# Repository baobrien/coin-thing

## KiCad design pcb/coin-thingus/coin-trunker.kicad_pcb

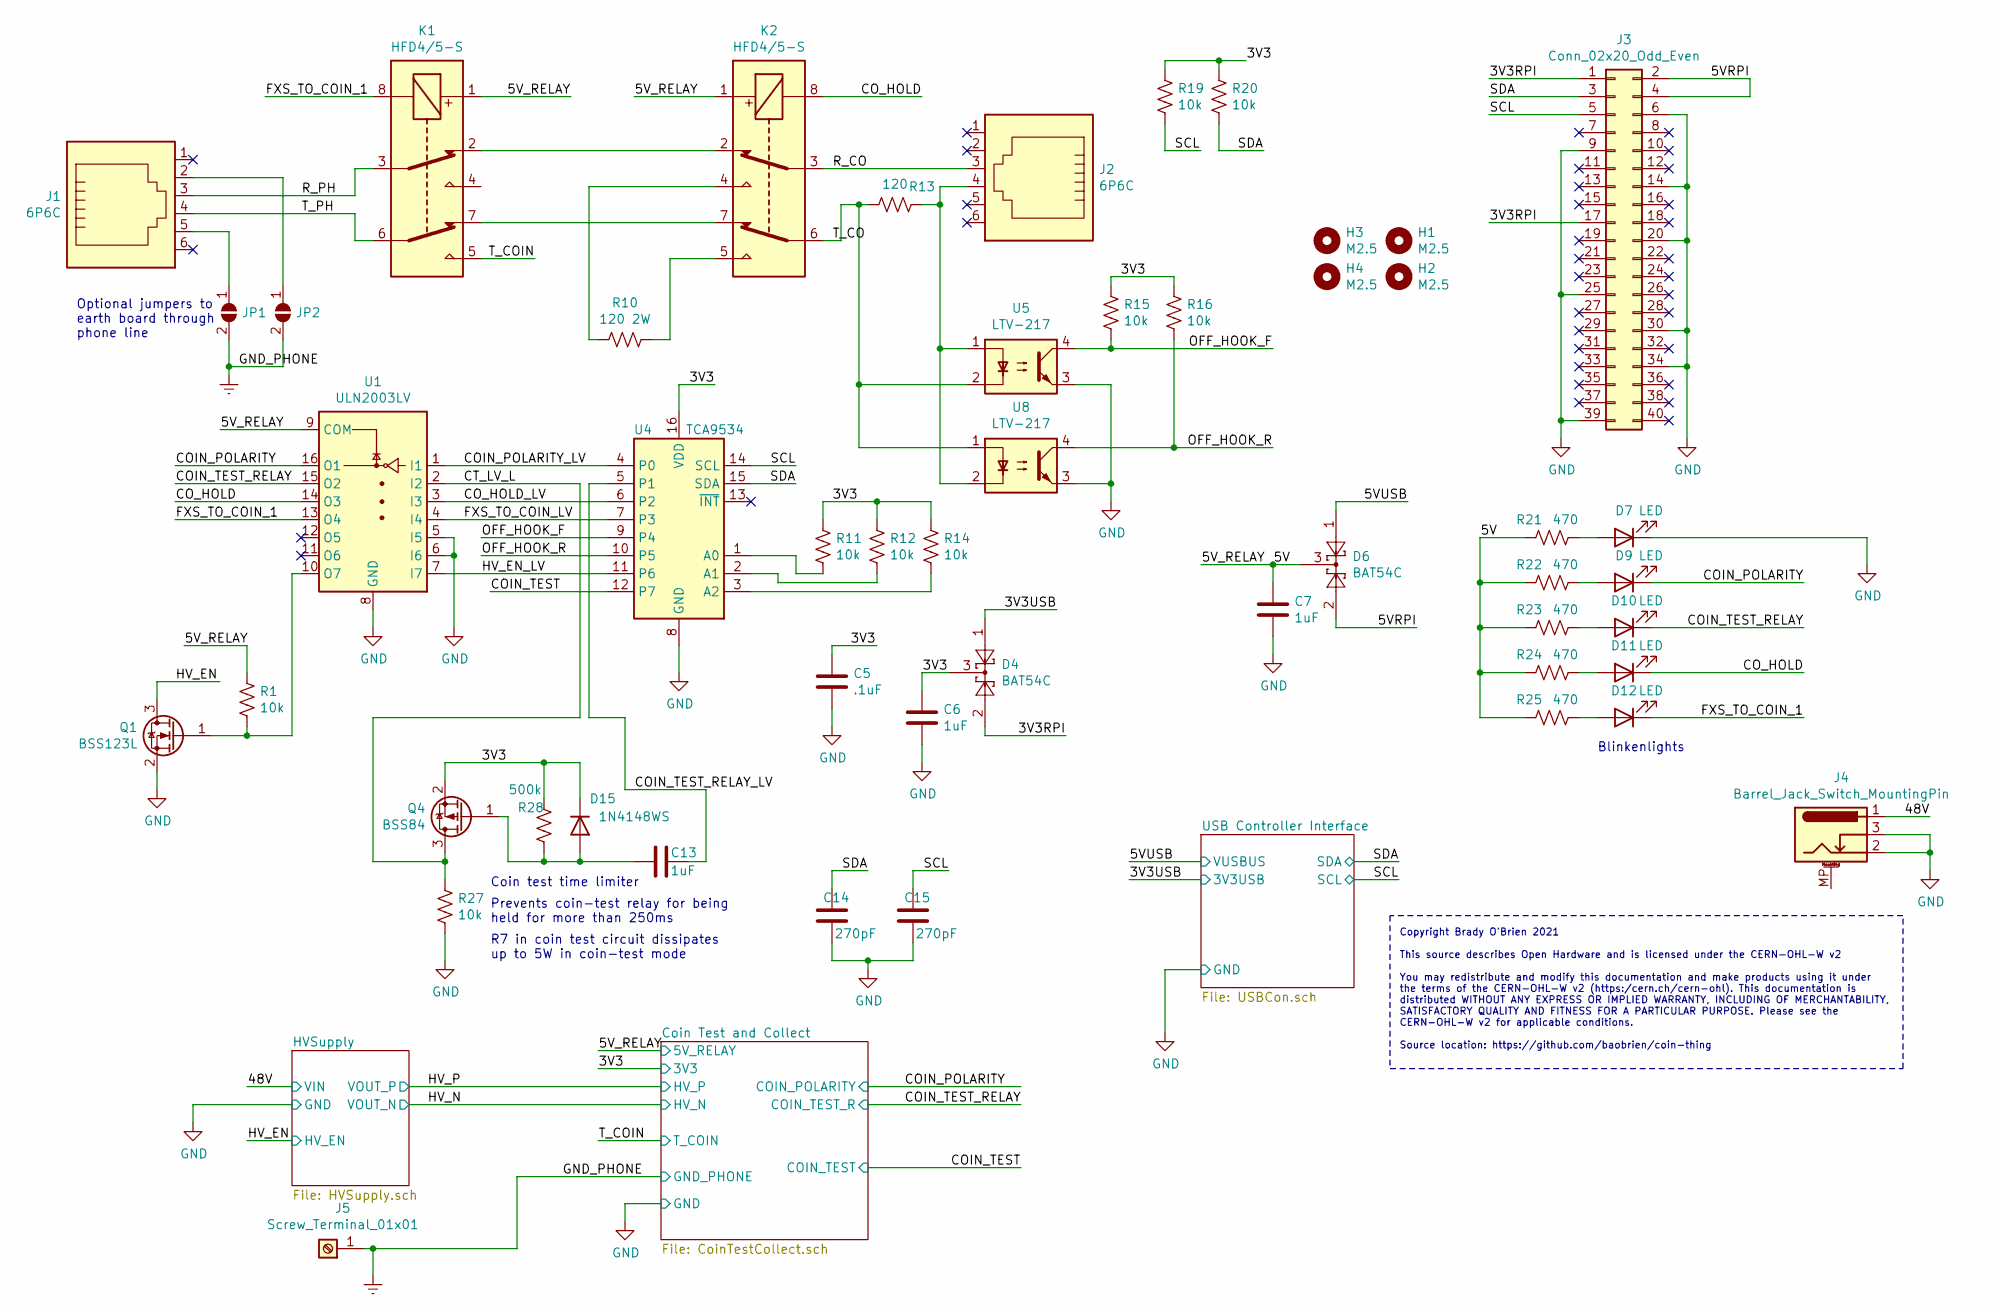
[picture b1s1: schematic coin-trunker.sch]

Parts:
C5: .1uF; C_0603_1608Metric
C6, C7, C13: 1uF; C_0603_1608Metric
C14, C15: 270pF; C_0603_1608Metric
D4, D6: BAT54C; SOT-23
D7, D9, D10, D11, D12: LED; LED_0603_1608Metric
D15: 1N4148WS; D_SOD-323_HandSoldering
H1, H2, H3, H4: M2.5; MountingHole_2.7mm_M2.5_Pad
J1, J2: 6P6C; RJ12_Molex_95501-6669
J3: Conn_02x20_Odd_Even; PinHeader_2x20_P2.54mm_Vertical
J4: Barrel_Jack_Switch_MountingPin; BarrelJack_CUI_PJ-102AH_Horizontal; Part PJ-102AH
J5: Screw_Terminal_01x01; screw_block_m3_5x7
JP1, JP2: SolderJumper_2_Open; SolderJumper-2_P1.3mm_Open_TrianglePad1.0x1.5mm
K1, K2: HFD4/5-S; Relay_DPDT_Omron_G6K-2F-Y
Q1: BSS123L; SOT-23
Q4: BSS84; SOT-23
R1, R11, R12, R14, R15, R16, R19, R20, R27: 10k; R_0402_1005Metric
R10: 120 2W; R_1206_3216Metric
R13: 120; R_0402_1005Metric
R21, R22, R23, R24, R25: 470; R_0402_1005Metric
R28: 500k; R_0402_1005Metric
U1: ULN2003LV; SOIC-16_3.9x9.9mm_P1.27mm
U4: TCA9534; TSSOP-16_4.4x5mm_P0.65mm
U5, U8: LTV-217; SOP-4_4.4x2.6mm_P1.27mm

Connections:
/3V3: C5.1, C6.1, D4.3, D15.1 (K), Q4.2 (S), R11.2, R12.2, R14.2, R15.2, R16.2, R19.2, R20.2, R28.1, U4.16 (VDD); also elsewhere on the board
/3V3RPI: D4.2, J3.1, J3.17
/3V3USB: D4.1; also elsewhere on the board
/5V: C7.1, D6.3, K1.1, K2.1, R1.1, R21.2, R22.2, R23.2, R24.2, R25.2, U1.9 (COM); also elsewhere on the board
/5VRPI: D6.2, J3.2, J3.4
/5VUSB: D6.1; also elsewhere on the board
/48V: J4.1; also elsewhere on the board
/COIN_POLARITY: D9.1 (K), U1.16 (O1); also elsewhere on the board
/COIN_POLARITY_LV: U1.1 (I1), U4.4 (P0)
/COIN_TEST: U4.12 (P7); also elsewhere on the board
/COIN_TEST_RELAY: D10.1 (K), U1.15 (O2); also elsewhere on the board
/COIN_TEST_RELAY_LV: C13.1, U4.5 (P1)
/CO_HOLD: D11.1 (K), K2.8, U1.14 (O3)
/CO_HOLD_LV: U1.3 (I3), U4.6 (P2)
/CT_LV_L: Q4.3 (D), R27.1, U1.2 (I2)
/FXS_TO_COIN_1: D12.1 (K), K1.8, U1.13 (O4)
/FXS_TO_COIN_LV: U1.4 (I4), U4.7 (P3)
/HV_EN: Q1.3 (D); also elsewhere on the board
/HV_EN_LV: U1.7 (I7), U4.11 (P6)
/OFF_HOOK_F: R15.1, U4.9 (P4), U5.4
/OFF_HOOK_R: R16.1, U4.10 (P5), U8.4
/R_CO: J2.3, K2.3
/R_PH: J1.3, K1.3
/SCL: C15.2, J3.5, R19.1, U4.14 (SCL); also elsewhere on the board
/SDA: C14.2, J3.3, R20.1, U4.15 (SDA); also elsewhere on the board
/T_CO: K2.6, R13.1, U5.2, U8.1
/T_COIN: K1.5; also elsewhere on the board
/T_PH: J1.4, K1.6
Earth: J5.1, JP1.2 (B), JP2.2 (B); also elsewhere on the board
GND: C5.2, C6.2, C7.2, C14.1, C15.1, D7.1 (K), J3.6, J3.9, J3.14, J3.20, J3.25, J3.30, J3.34, J3.39, J4.2, J4.3, Q1.2 (S), R27.2, U1.5 (I5), U1.6 (I6), U1.8 (GND), U4.8 (GND), U5.3, U8.3; also elsewhere on the board
unnamed: C13.2, D15.2 (A), Q4.1 (G), R28.2
unnamed: D7.2 (A), R21.1
unnamed: D9.2 (A), R22.1
unnamed: D10.2 (A), R23.1
unnamed: D11.2 (A), R24.1
unnamed: D12.2 (A), R25.1
unnamed: J1.2, JP2.1 (A)
unnamed: J1.5, JP1.1 (A)
unnamed: J2.4, R13.2, U5.1, U8.2
unnamed: K1.2, K2.2
unnamed: K1.7, K2.7
unnamed: K2.4, R10.2
unnamed: K2.5, R10.1
unnamed: Q1.1 (G), R1.2, U1.10 (O7)
unnamed: R11.1, U4.1 (A0)
unnamed: R12.1, U4.2 (A1)
unnamed: R14.1, U4.3 (A2)

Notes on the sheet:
Copyright Brady O’Brien 2021 This source describes Open Hardware and is licensed under the CERN-OHL-W v2 You may redistribute and modify this documentation and make products using it under the terms of the CERN-OHL-W v2 (https:/cern.ch/cern-ohl). This documentation is distributed WITHOUT ANY EXPRES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
Blinkenlights
Optional jumpers to earth board through phone line
Coin test time limiter
Prevents coin-test relay for being held for more than 250ms
R7 in coin test circuit dissipates up to 5W in coin-test mode

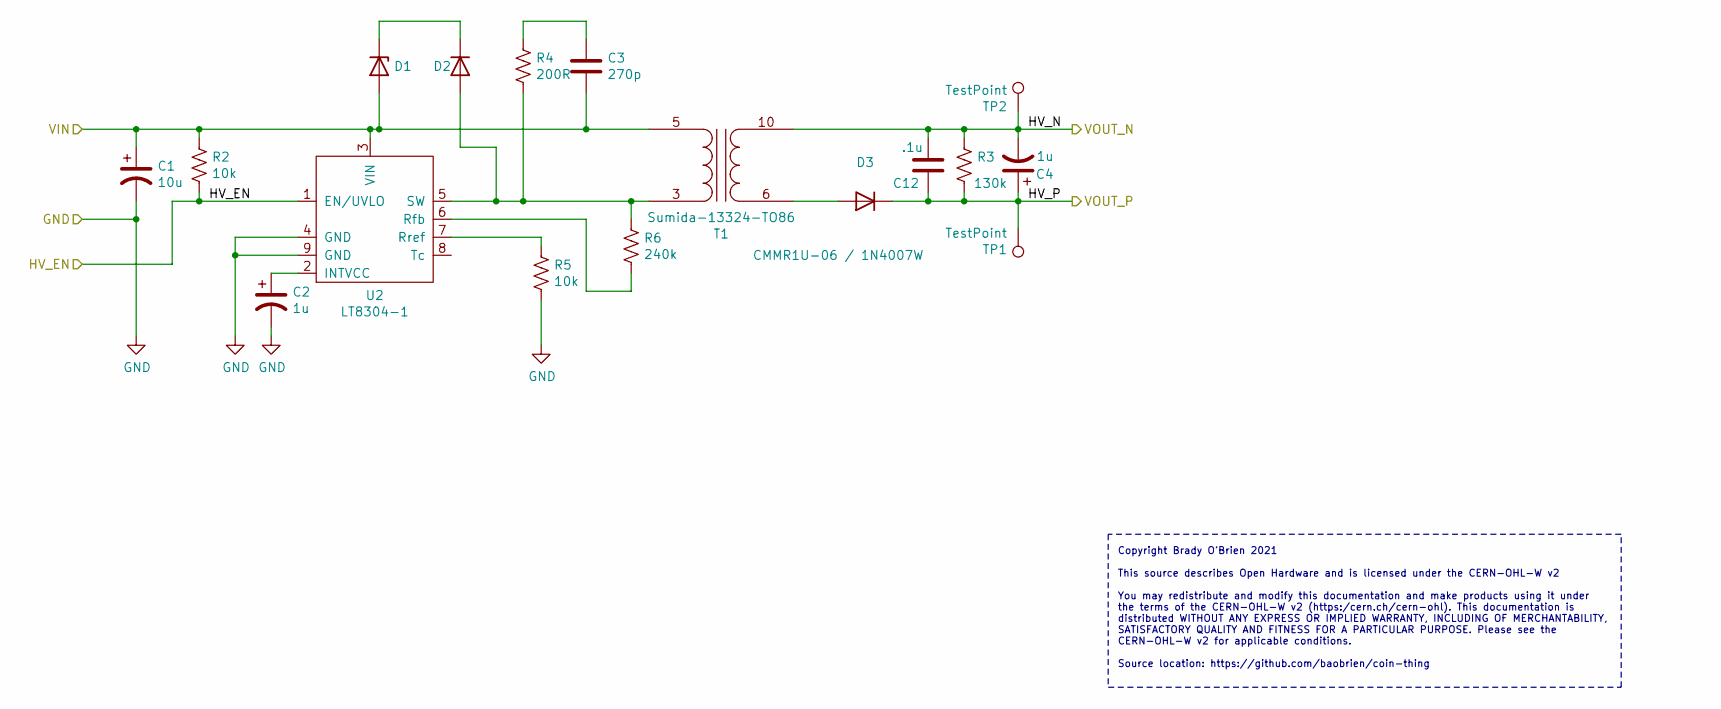
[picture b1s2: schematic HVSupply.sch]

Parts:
C1: 10u; C_1210_3225Metric
C2: 1u; C_0603_1608Metric
C3: 270p; C_0603_1608Metric
C4: 1u; CP_Radial_D6.3mm_P2.50mm
C12: .1u; C_1210_3225Metric
D1: D_Zener; D_SMA
D2: DFLS1150-7; D_PowerDI-123
D3: CMMR1U-06 / 1N4007W; D_SOD-123F; Part CMMR1U-06
R2, R5: 10k; R_0402_1005Metric
R3: 130k; R_0402_1005Metric
R4: 200R; R_0402_1005Metric
R6: 240k; R_0603_1608Metric
T1: Sumida-13324-TO86; SUMIDA-S-074-1511
TP1, TP2: TestPoint; Pin_D1.0mm_L10.0mm
U2: LT8304-1; TI_SO-PowerPAD-8

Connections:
/48V: C1.1, C3.2, D1.2 (A), R2.2, T1.5 (AB), U2.3 (VIN); also elsewhere on the board
/HV_EN: R2.1, U2.1 (EN/UVLO); also elsewhere on the board
/HV_N: C4.2, C12.1, R3.1, T1.10 (SA), TP2.1; also elsewhere on the board
/HV_P: C4.1, C12.2, D3.1 (K), R3.2, TP1.1; also elsewhere on the board
GND: C1.2, C2.2, R5.1, U2.4 (GND), U2.9 (GND); also elsewhere on the board
unnamed: C2.1, U2.2 (INTVCC)
unnamed: C3.1, R4.2
unnamed: D1.1 (K), D2.1 (K)
unnamed: D2.2 (A), R4.1, R6.1, T1.3 (AA), U2.5 (SW)
unnamed: D3.2 (A), T1.6 (SB)
unnamed: R5.2, U2.7 (Rref)
unnamed: R6.2, U2.6 (Rfb)

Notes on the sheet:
Copyright Brady O’Brien 2021 This source describes Open Hardware and is licensed under the CERN-OHL-W v2 You may redistribute and modify this documentation and make products using it under the terms of the CERN-OHL-W v2 (https:/cern.ch/cern-ohl). This documentation is distributed WITHOUT ANY EXPRES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

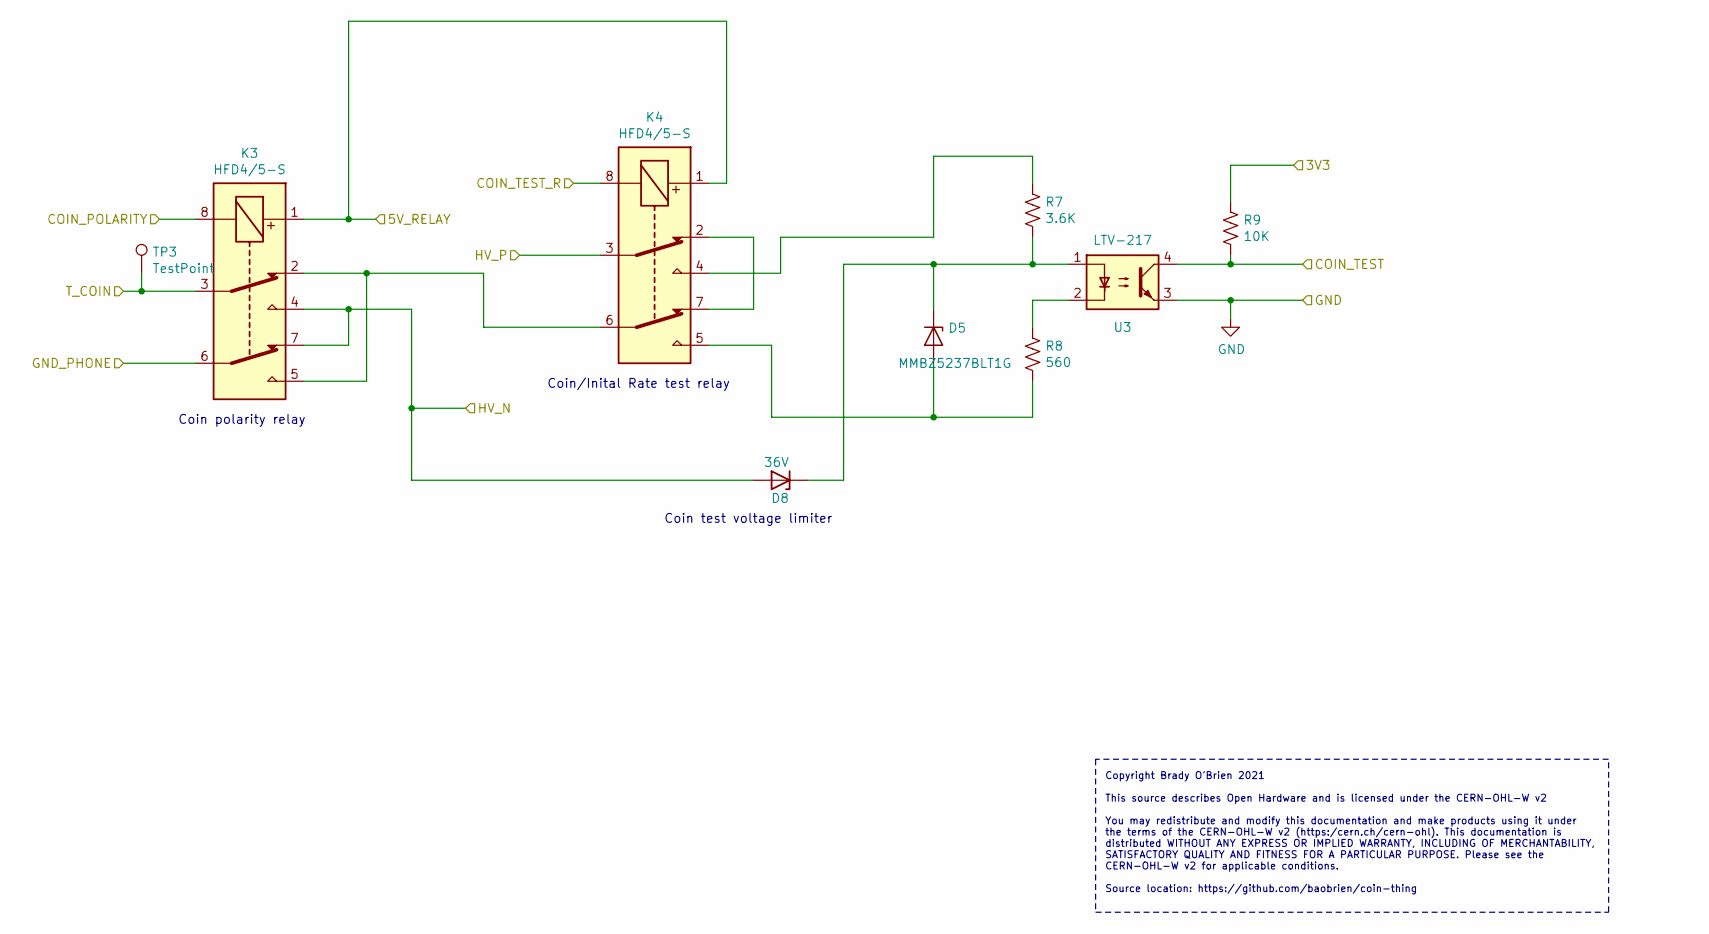
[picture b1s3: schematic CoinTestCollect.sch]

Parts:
D5: MMBZ5237BLT1G; SOT-23; Part MMBZ5237BLT1G
D8: 36V; D_SOD-323_HandSoldering; Part BZX384-C36
K3, K4: HFD4/5-S; Relay_DPDT_Omron_G6K-2F-Y
R7: 3.6K; R_2010_5025Metric; Part 2010W2J0392T4S
R8: 560; R_0603_1608Metric
R9: 10K; R_0402_1005Metric
TP3: TestPoint; Pin_D1.0mm_L10.0mm
U3: LTV-217; SOP-4_4.4x2.6mm_P1.27mm

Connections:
/3V3: R9.1; also elsewhere on the board
/5V: K3.1, K4.1; also elsewhere on the board
/COIN_POLARITY: K3.8; also elsewhere on the board
/COIN_TEST: R9.2, U3.4; also elsewhere on the board
/COIN_TEST_RELAY: K4.8; also elsewhere on the board
/HV_N: D8.2 (A), K3.4, K3.7; also elsewhere on the board
/HV_P: K4.3; also elsewhere on the board
/T_COIN: K3.3, TP3.1; also elsewhere on the board
Earth: K3.6; also elsewhere on the board
GND: U3.3; also elsewhere on the board
unnamed: D5.1 (A), K4.5, R8.2
unnamed: D5.3 (K), D8.1 (K), R7.2, U3.1
unnamed: K3.2, K3.5, K4.6
unnamed: K4.2, K4.7
unnamed: K4.4, R7.1
unnamed: R8.1, U3.2

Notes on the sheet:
Coin polarity relay
Coin/Inital Rate test relay
Coin test voltage limiter
Copyright Brady O’Brien 2021 This source describes Open Hardware and is licensed under the CERN-OHL-W v2 You may redistribute and modify this documentation and make products using it under the terms of the CERN-OHL-W v2 (https:/cern.ch/cern-ohl). This documentation is distributed WITHOUT ANY EXPRES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

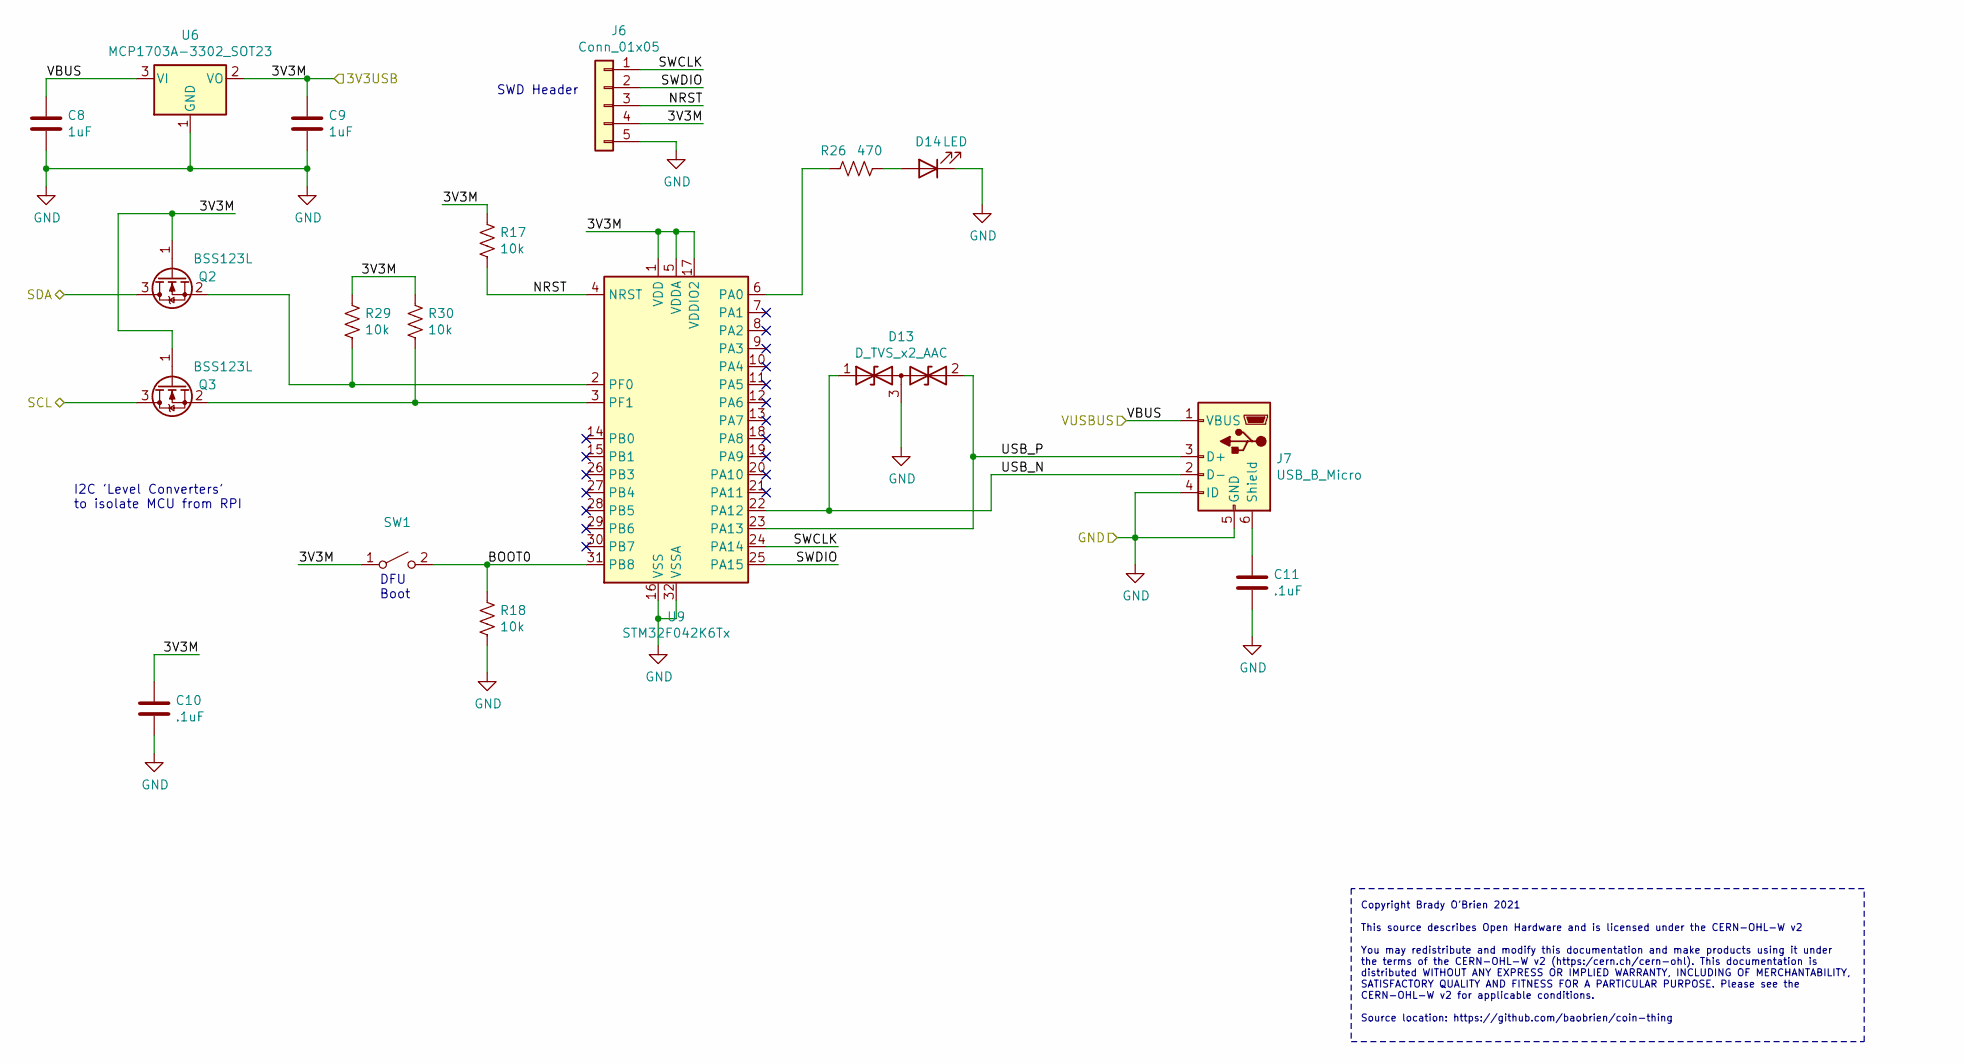
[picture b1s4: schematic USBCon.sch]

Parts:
C8, C9: 1uF; C_0603_1608Metric
C10, C11: .1uF; C_0603_1608Metric
D13: D_TVS_x2_AAC; SOT-23
D14: LED; LED_0603_1608Metric
J6: Conn_01x05; PinHeader_1x05_P2.54mm_Vertical
J7: USB_B_Micro; USB_Micro-B_Molex-105017-0001; Part U254-051T-4BH23-S2B
Q2, Q3: BSS123L; SOT-23
R17, R18, R29, R30: 10k; R_0402_1005Metric
R26: 470; R_0402_1005Metric
SW1: TS-1187A-C-E-B; SW_SPST_TL3342; Part TS-1187A-C-E-B
U6: MCP1703A-3302_SOT23; SOT-23; Part Alt SC662K-3.3V
U9: STM32F042K6Tx; LQFP-32_7x7mm_P0.8mm

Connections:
/3V3USB: C9.1, C10.1, J6.4, Q2.1 (G), Q3.1 (G), R17.1, R29.1, R30.1, SW1.1 (A), U6.2 (VO), U9.1 (VDD), U9.5 (VDDA), U9.17 (VDDIO2); also elsewhere on the board
/5VUSB: C8.1, J7.1 (VBUS), U6.3 (VI); also elsewhere on the board
/SCL: Q3.3 (D); also elsewhere on the board
/SDA: Q2.3 (D); also elsewhere on the board
/USB Controller Interface/BOOT0: R18.1, SW1.2 (B), U9.31 (PB8)
/USB Controller Interface/NRST: J6.3, R17.2, U9.4 (NRST)
/USB Controller Interface/SWCLK: J6.1, U9.24 (PA14)
/USB Controller Interface/SWDIO: J6.2, U9.25 (PA15)
/USB Controller Interface/USB_N: D13.1 (A1), J7.2 (D-), U9.22 (PA12)
/USB Controller Interface/USB_P: D13.2 (A2), J7.3 (D+), U9.23 (PA13)
GND: C8.2, C9.2, C10.2, C11.2, D13.3 (common), D14.1 (K), J6.5, J7.4 (ID), J7.5 (GND), R18.2, U6.1 (GND), U9.16 (VSS), U9.32 (VSSA); also elsewhere on the board
unnamed: C11.1, J7.6 (Shield)
unnamed: D14.2 (A), R26.1
unnamed: Q2.2 (S), R29.2, U9.2 (PF0)
unnamed: Q3.2 (S), R30.2, U9.3 (PF1)
unnamed: R26.2, U9.6 (PA0)

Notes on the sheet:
Copyright Brady O’Brien 2021 This source describes Open Hardware and is licensed under the CERN-OHL-W v2 You may redistribute and modify this documentation and make products using it under the terms of the CERN-OHL-W v2 (https:/cern.ch/cern-ohl). This documentation is distributed WITHOUT ANY EXPRES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
DFU Boot
SWD Header
I2C 'Level Converters' to isolate MCU from RPI

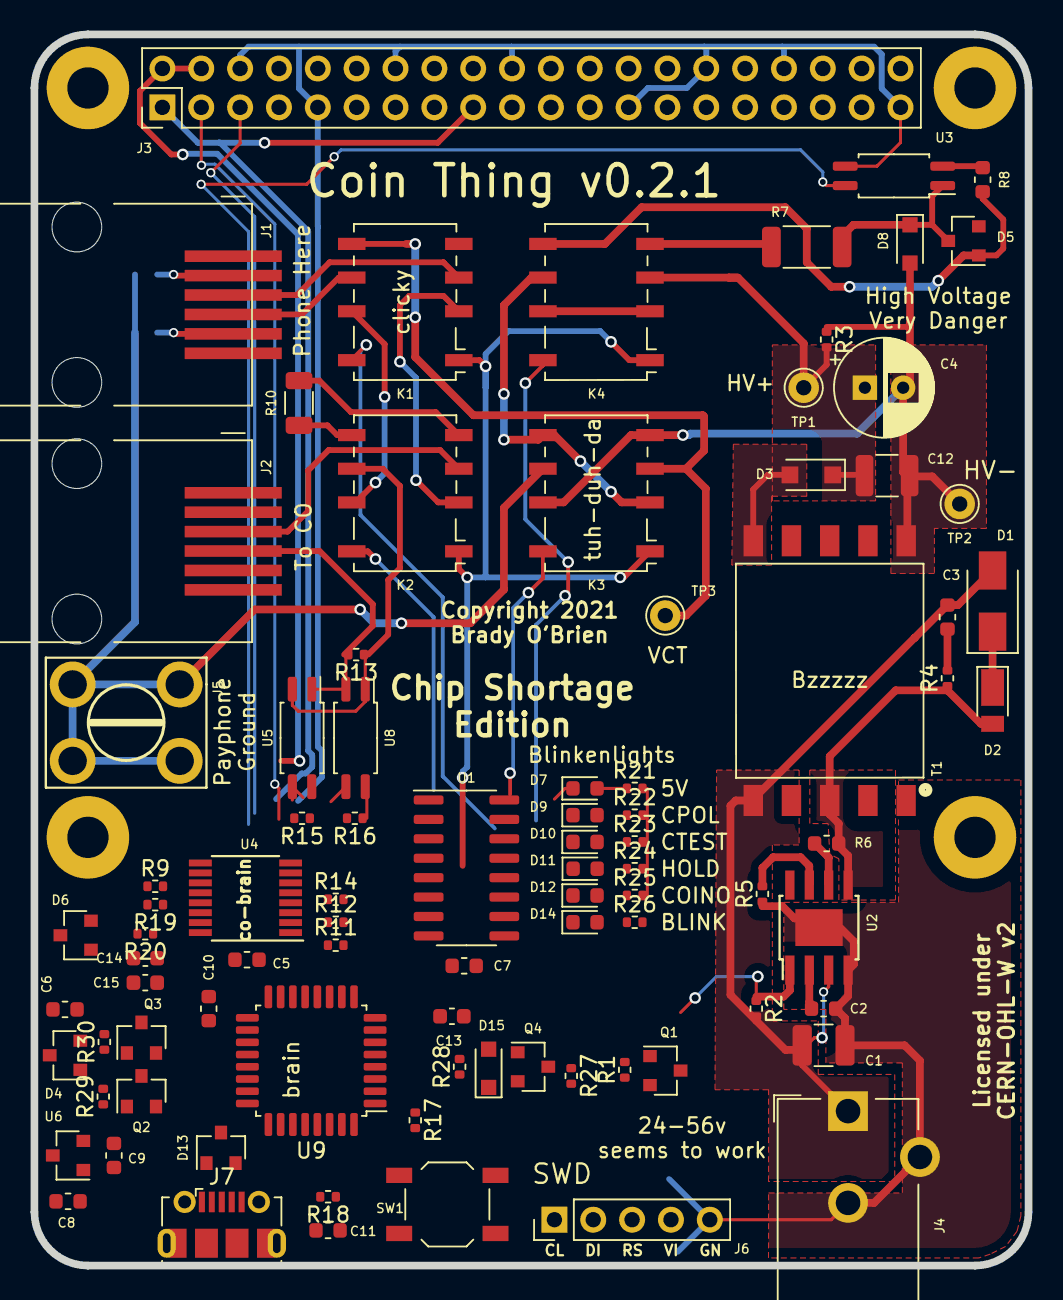
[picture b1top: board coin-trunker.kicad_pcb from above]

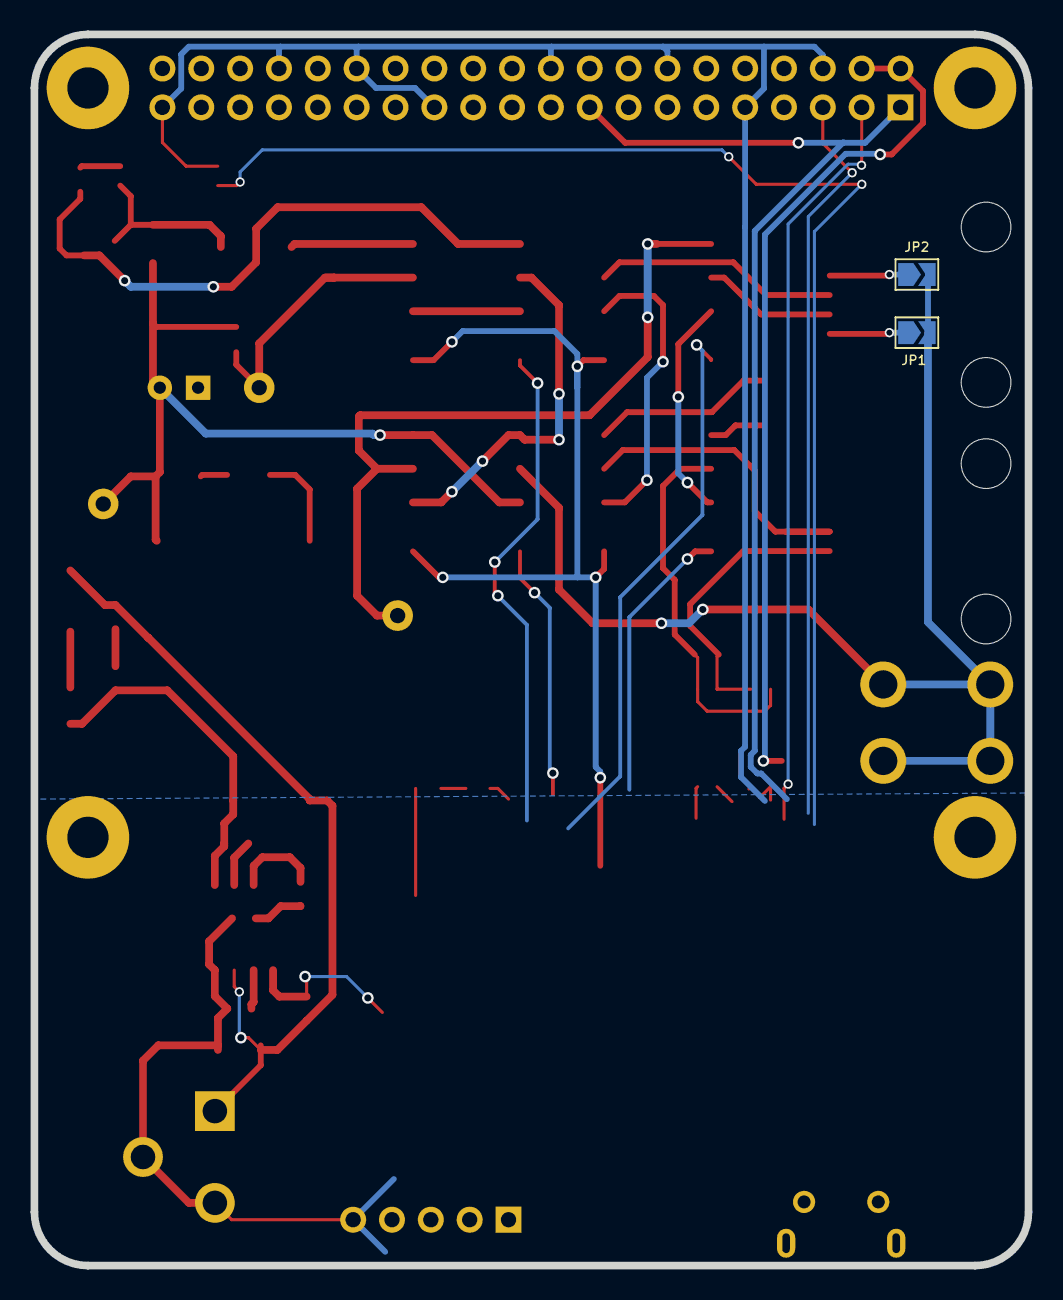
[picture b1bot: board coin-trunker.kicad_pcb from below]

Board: 2 copper layers, 65.0 x 80.5 mm, 94 parts (2 on the bottom side), 73 nets.

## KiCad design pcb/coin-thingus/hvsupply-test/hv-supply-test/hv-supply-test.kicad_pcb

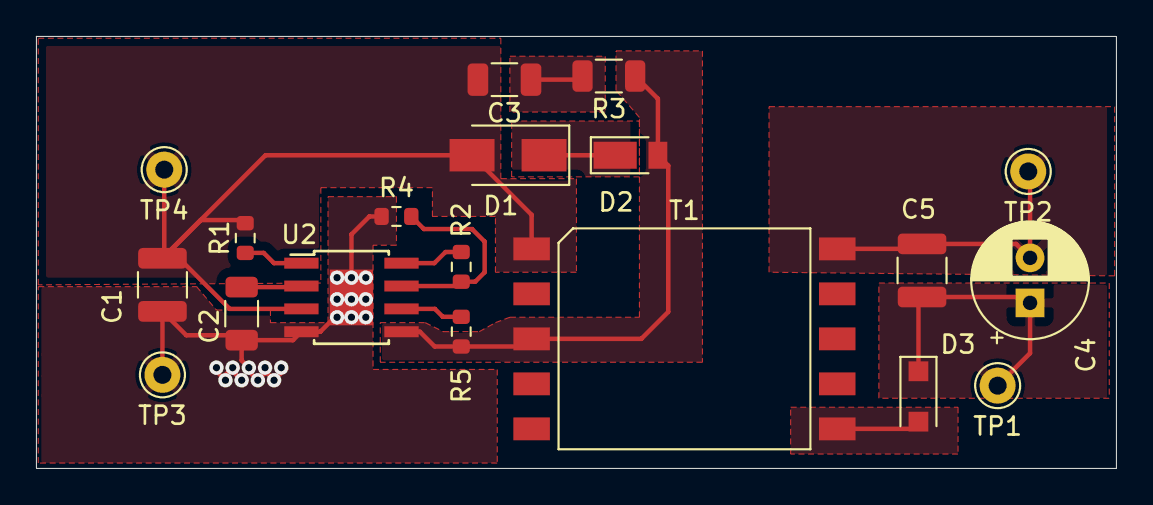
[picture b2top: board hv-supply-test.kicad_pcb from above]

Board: 2 copper layers, 60.0 x 24.0 mm, 19 parts (0 on the bottom side), 13 nets.

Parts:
C1: 10u; C_1210_3225Metric
C2: 1u; C_1206_3216Metric
C3: 270p; C_1206_3216Metric
C4: 1u; CP_Radial_D6.3mm_P2.50mm
C5: .1u; C_1210_3225Metric
D1: D_Zener; D_SMA
D2: DFLS1150-7; D_PowerDI-123
D3: CMMR1U-06; D_SOD-123F
R1, R4: 10k; R_0603_1608Metric
R2: 100k; R_0603_1608Metric
R3: 200R; R_1206_3216Metric
R5: 200k; R_0603_1608Metric
T1: Sumida-13324-TO86; SUMIDA-S-074-1511
TP1, TP2, TP3, TP4: TestPoint; Pin_D1.0mm_L10.0mm
U2: LT8304; TI_SO-PowerPAD-8

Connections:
/HV_EN: R1.1, U2.1
/VIN: C1.1, C3.2, D1.2, R1.2, T1.5, TP4.1, U2.3
/VOUT_N: C4.2, C5.2, T1.6, TP2.1
/VOUT_P: C4.1, C5.1, D3.1, TP1.1
GND: C1.2, C2.2, R4.1, TP3.1, U2.4, U2.9
unnamed: C2.1, U2.2
unnamed: C3.1, R3.2
unnamed: D1.1, D2.1
unnamed: D2.2, R3.1, R5.1, T1.3, U2.5
unnamed: D3.2, T1.10
unnamed: R2.1, U2.8
unnamed: R2.2, R4.2, U2.7
unnamed: R5.2, U2.6

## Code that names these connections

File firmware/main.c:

/*
 * This file is part of the libopencm3 project.
 *
 * Copyright (C) 2010 Gareth McMullin <gareth@blacksphere.co.nz>
 *
 * This library is free software: you can redistribute it and/or modify
 * it under the terms of the GNU Lesser General Public License as published by
 * the Free Software Foundation, either version 3 of the License, or
 * (at your option) any later version.
 *
 * This library is distributed in the hope that it will be useful,
 * but WITHOUT ANY WARRANTY; without even the implied warranty of
 * MERCHANTABILITY or FITNESS FOR A PARTICULAR PURPOSE.  See the
 * GNU Lesser General Public License for more details.
 *
 * You should have received a copy of the GNU Lesser General Public License
 * along with this library.  If not, see <http://www.gnu.org/licenses/>.
 */

#include <stdlib.h>

#include <libopencm3/stm32/rcc.h>
#include <libopencm3/stm32/gpio.h>
#include <libopencm3/stm32/i2c.h>
#include <libopencm3/usb/usbd.h>
#include <libopencm3/usb/cdc.h>
#include <libopencm3/cm3/scb.h>
#include <libopencm3/stm32/f0/syscfg.h>

#include "usb_stuff.h"
#include "notdumbi2c.h"
#include "localsystick.h"
#include "gpio_tca9534a.h"
#include "cointhingus.h"

int main(void)
{
    int i;

    usbd_device *usbd_dev;

    usb_setup(&usbd_dev);

    i2c_setup();

    systick_setup();

    ggpio_dev tca9534;
    // ggpio_pin coin_pol, coin_test, co_hold, fxs_to_coin_1;
    ggpio_init_tca9534(&tca9534, I2C1, 0x3F);
    cointhing coin;
    cointhing_channel *ch;
    ct_init_cointhingusv1(&coin, &tca9534);
    ct_hvpsu_disable(&coin);
    ch = &coin.channels[0];

    // while(1) {
    //     ct_collect(ch);
    //     delayms(1000);
    //     ct_return(ch);
    //     delayms(1000);
    //     ct_test_minrate(ch);
    //     delayms(1000);
    //     ct_test_present(ch);
    //     delayms(1000);
    // }

    while (1) {
        usbd_poll(usbd_dev);
        if (ct_offhook(ch)) {
            while (ct_offhook(ch)) {
                usbd_poll(usbd_dev);
            }
            delayms(30);
            while (ct_offhook(ch) == PHONE_OFFHOOK_FWD) {
                usbd_poll(usbd_dev);
            }
            ct_hvpsu_enable(&coin);
            if (ct_test_present(ch)) {
                if (ct_test_minrate(ch)) {
                    ct_return(ch);
                } else {
                    ct_collect(ch);
                }
            }
            ct_hvpsu_disable(&coin);
        }
    }

    delayms(100);
    while (1)
        usbd_poll(usbd_dev);
}

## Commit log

2021-01-27 Release version 0.1.0
2021-02-14 v0.1 release
2021-02-14 Add CERN-OHL-W v2 license
2021-02-14 Some work towards v0.2
2021-03-13 HV test board; A bunch of work towards v0.2
2021-03-14 First commit of firmware
2021-03-21 Bunch'o work towards v0.2
2021-03-25 Coin thing v0.2 PCB
2021-04-11 V0.2 as ordered
2021-04-16 Start work on alternate micro

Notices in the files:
pcb/coin-thingus/coin-trunker.kicad_pcb:
Copyright 2021
